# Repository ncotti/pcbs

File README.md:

# PCBS

PCB boards designed with KiCad.

https://www.youtube.com/watch?v=Poj4V9u9bMg

## Version numbering

V0.X

Refers to prototypes that have not being produced, soldered and tested. Being v0.0 the first prototype.

V1.0 is the version of the schematic that has been produced and tested.

V1.x are iterations of a working design.

v2.x are versions that changed something substancial.

## Best way to share libraries between projects

So, you have your library in a defined path, and you go to File->Add library.

When doing this, you will see that the library has been added with an absolute path (Preferences -> Manage Footprint libraries).

The steps to take are as follows:

Open the project. Go to "Preferences -> Configure Paths..." and define these three new variables:

| Name                      | Path                          |
|:--------------------------|:------------------------------|
| KICAD_USER_SYMBOL_DIR     | <path_to_library>/symbols     |
| KICAD_USER_FOOTPRINT_DIR  | <path_to_library>/footprints  |
| KICAD_USER_3DMODEL_DIR    | <path_to_library>/3d_models   |

After that, the libraries should be loaded.

### Creating new libraries steps

You can create a new library like "File -> New Library... -> Global". Then, choose the name you like, and save it in `<path_to_library>/symbols/<lib_name>`.

If you previously defined the environmental variables, KICAD will autocomplete the path with ${KICAD_USER_SYMBOL_DIR}/<lib_name>. Go check it out at "Preferences -> Manage Symbol Libraries".

Then, go to the "Footprint Editor". The same procedure as with the symbol libraries apply.

Finally, when importing 3D files, the enviromental variable should also autocomplete with `${KICAD_USER_3DMODEL_DIR}/<3d_file>`.

### Footprint parts: M L normal

When importing footprints, some appear with "M" "L" or normal.

This letters stand for:

* M: Most land protrusion (bigger pads)
* N (or no letter): Nominal land protrusion (normal pads)
* L: Least land protrusion (smaller pads)

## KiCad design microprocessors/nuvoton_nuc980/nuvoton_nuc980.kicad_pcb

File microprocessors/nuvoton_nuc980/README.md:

# NUC980

Documentation:

https://www.nuvoton.com/products/microprocessors/arm9-mpus/nuc980-industrial-control-iot-series/nuc980dk63yc/?group=Document&tab=2

NuMaker-IIoT-NUC980

https://www.techdesign.com/market/nuvoton/product-detail/ntc000092/numaker-iiot-nuc980?packing=No%20Packing

https://www.nuvoton.com/products/iot-solution/iot-platform/numaker-iiot-nuc980/

## Parallel LDOs

https://techweb.rohm.com/product/power-ic/dcdc/9235/

You can't connect the two LDO outputs together, because you can't guaranty that both will have exactly the same voltage value.

Following the diagram above, we can expect the middle point, after the ballast resistors, to be at the same "Vout" potential:

$$ V_{out} = V_1 - I_1 \cdot R = V_2 - I_2 \cdot R$$

$$ R = \frac{V_2 - V_1}{I_2 - I_1}$$

We go to the datasheet and find the "CD output accuracy"

We want two metrics here: 

1. Voltage range at the output.
2. Maximum current at the output.

The worst case would be:

$$V_2 = V_{0} + \Delta V $$
$$V_1 = V_{0} - \Delta V $$

$$ R = \frac{2 \cdot \Delta V}{I_2 - I_1} $$

It would be great to say: "hey make the current difference equal to 0". However, that would imply a value of "R" infinitely big.

The bigger "R", the more equal the currents are. However, the bigger the R, the bigger the voltage drop at the output.

Given a desired output current $I_{out}$, which must be greater than the maximum current of the LDO $I_{LDO}$, the difference in current must be less than the current required by the two LDOs.

For example, if LDO max current is 300 mA, and I want 500mA, then the difference must be less than 100mA, because one will be providing 300mA and the other 200mA.

$$(\Delta I = \frac{2\Delta V}{R} ) \le 2\cdot I_{max} - I_{out} $$

$$ R \ge \frac{2\Delta V}{2\cdot I_{max} - I_{out}} $$

Then:

$$ I_{out} = I_1 + I_2 = \frac{V_1 - V_{out}}{R} + \frac{V_2 - V_{out}}{R} $$

$$ I_{out} = \frac{V_0 - \Delta V - V_{out}}{R} + \frac{V_0 + \Delta V - V_{out}}{R}$$

$$ I_{out} = 2 \frac{V_0 - V_{out}}{R} $$

$$ V_0 - V_{out} = I_{out} \cdot R / 2 $$

Other design parameter is how much you desire the output voltage to swing. If the accuracy of the LDO is 1%, well maybe you can afford to lose 3% or 5%, depending on the minimum voltage required by your devices:

$$ (\Delta V_{out-actual} = I_{out} \cdot R / 2) \le \Delta V_{out} $$

Despejando "R":

$$ R \le \frac{2 \Delta V_{out}}{I_{out}}$$

Therefore:

$$\frac{2\Delta V}{2\cdot I_{max} - I_{out}} \le R \le \frac{2 \Delta V_{out}}{I_{out}} $$

And that's the design equation:

Your inputs are:

* $\Delta V_{out}$: Maximum tolerated voltage drop from the nominal voltage of the LDO at the output.
* $I_{out}$: Maximum current consumed by the load.

And then $\Delta V$ and $I_{max}$ are the precision and maximum current of the LDO as stated in the datasheet.

You always want the minimum value of "R" possible, that still satisfies the inequation.

If using:

$$ 2 * 3.3 * 0.014 / (2 * 300m - 450m) < R < 2 * 200m / 450m$$

$$ 0.616 <= R <= 0.89 $$

https://www.youtube.com/watch?v=H4nrotIVuUM

https://abracon.com/uploads/resources/Ferrite-Beads-White-Paper.pdf

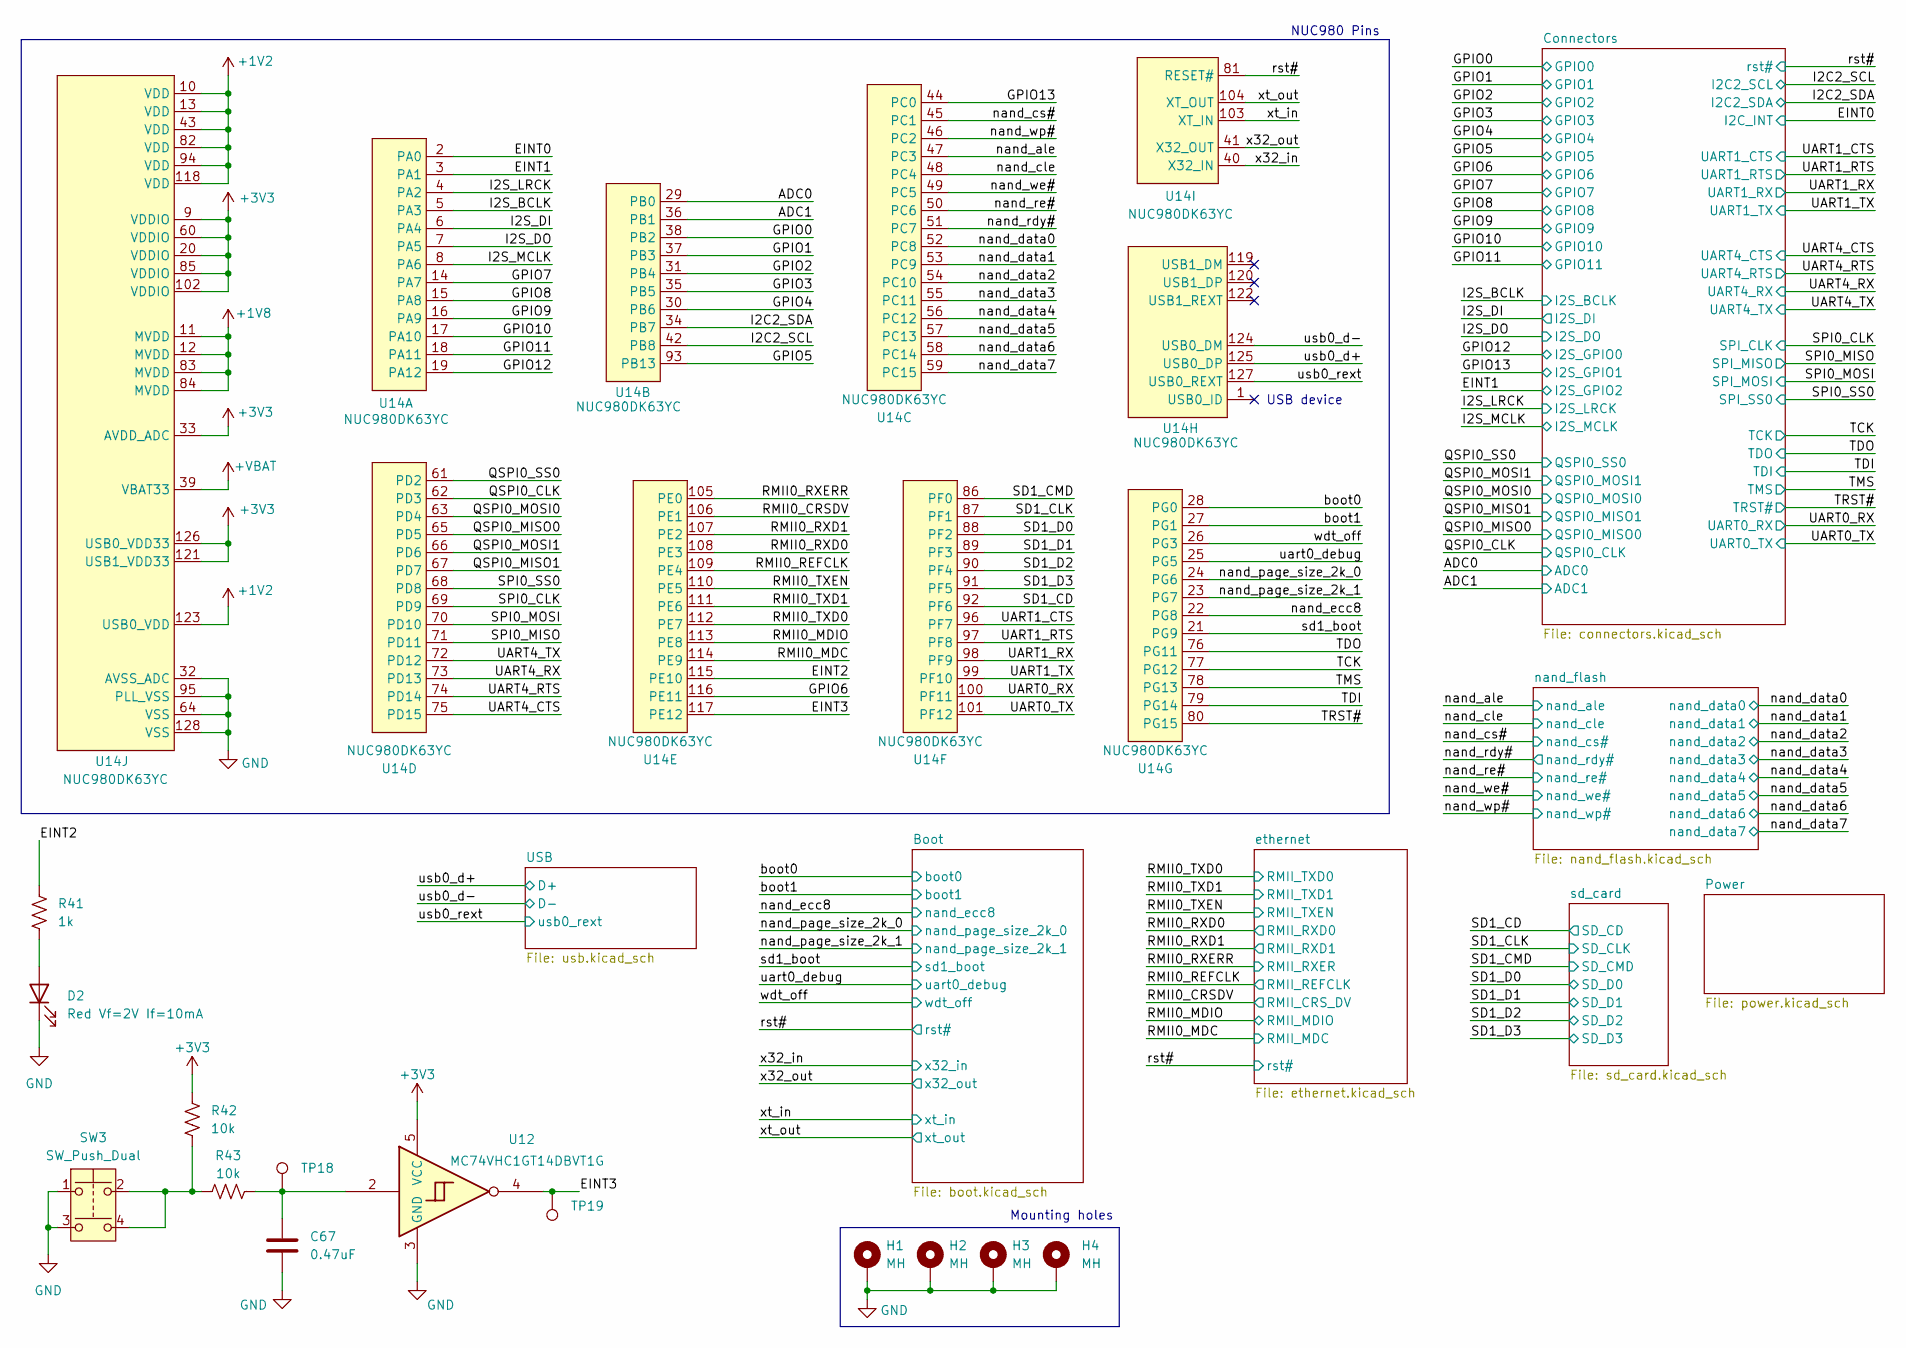
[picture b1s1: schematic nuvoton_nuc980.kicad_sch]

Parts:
C67: 0.47uF; C_0805_2012Metric_Pad1.18x1.45mm_HandSolder; Mfr. P/N CL21B474KAFNNNG
D2: Red Vf=2V If=10mA; LED_0603_1608Metric_Pad1.05x0.95mm_HandSolder; Mfr. P/N B1911USD-20D000114U1930
H1, H2, H3, H4: MH
R41: 1k; R_0805_2012Metric_Pad1.20x1.40mm_HandSolder; Mfr. P/N RC0805FR-101KL
R42, R43: 10k; R_0805_2012Metric_Pad1.20x1.40mm_HandSolder; Mfr. P/N RC0805FR-1310KL
SW3: SW_Push_Dual; SW_PUSH_6mm_H5mm; Mfr. P/N TS02-66-60-BK-260-SCR-D
TP18, TP19: TestPoint; TestPoint_Pad_D2.0mm
U12: MC74VHC1GT14DBVT1G; SC-74A-5_1.55x2.9mm_P0.95mm; Mfr. P/N MC74VHC1GT14DBVT1G
U14: NUC980DK63YC; LQFP-128_14x14mm_P0.4mm; Mfr. P/N NUC980DK63YC; Digikey P/N 816-NUC980DK63YC-ND

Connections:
+1V2: U14.10 (VDD), U14.13 (VDD), U14.43 (VDD), U14.82 (VDD), U14.94 (VDD), U14.118 (VDD), U14.123 (USB0_VDD); also elsewhere on the board
+1V8: U14.11 (MVDD), U14.12 (MVDD), U14.83 (MVDD), U14.84 (MVDD); also elsewhere on the board
+3V3: R42.1, U12.5 (VCC), U14.9 (VDDIO), U14.20 (VDDIO), U14.33 (AVDD_ADC), U14.60 (VDDIO), U14.85 (VDDIO), U14.102 (VDDIO), U14.121 (USB1_VDD33), U14.126 (USB0_VDD33); also elsewhere on the board
+VBAT: U14.39 (VBAT33); also elsewhere on the board
/ADC0: U14.29 (PB0); also elsewhere on the board
/ADC1: U14.36 (PB1); also elsewhere on the board
/EINT0: U14.2 (PA0); also elsewhere on the board
/EINT1: U14.3 (PA1); also elsewhere on the board
/EINT2: R41.1, U14.115 (PE10)
/EINT3: TP19.1, U12.4, U14.117 (PE12)
/GPIO0: U14.38 (PB2); also elsewhere on the board
/GPIO1: U14.37 (PB3); also elsewhere on the board
/GPIO2: U14.31 (PB4); also elsewhere on the board
/GPIO3: U14.35 (PB5); also elsewhere on the board
/GPIO4: U14.30 (PB6); also elsewhere on the board
/GPIO5: U14.93 (PB13); also elsewhere on the board
/GPIO6: U14.116 (PE11); also elsewhere on the board
/GPIO7: U14.14 (PA7); also elsewhere on the board
/GPIO8: U14.15 (PA8); also elsewhere on the board
/GPIO9: U14.16 (PA9); also elsewhere on the board
/GPIO10: U14.17 (PA10); also elsewhere on the board
/GPIO11: U14.18 (PA11); also elsewhere on the board
/GPIO12: U14.19 (PA12); also elsewhere on the board
/GPIO13: U14.44 (PC0); also elsewhere on the board
/I2C2_SCL: U14.42 (PB8); also elsewhere on the board
/I2C2_SDA: U14.34 (PB7); also elsewhere on the board
/I2S_BCLK: U14.5 (PA3); also elsewhere on the board
/I2S_DI: U14.6 (PA4); also elsewhere on the board
/I2S_DO: U14.7 (PA5); also elsewhere on the board
/I2S_LRCK: U14.4 (PA2); also elsewhere on the board
/I2S_MCLK: U14.8 (PA6); also elsewhere on the board
/QSPI0_CLK: U14.62 (PD3); also elsewhere on the board
/QSPI0_MISO0: U14.65 (PD5); also elsewhere on the board
/QSPI0_MISO1: U14.67 (PD7); also elsewhere on the board
/QSPI0_MOSI0: U14.63 (PD4); also elsewhere on the board
/QSPI0_MOSI1: U14.66 (PD6); also elsewhere on the board
/QSPI0_SS0: U14.61 (PD2); also elsewhere on the board
/RMII0_CRSDV: U14.106 (PE1); also elsewhere on the board
/RMII0_MDC: U14.114 (PE9); also elsewhere on the board
/RMII0_MDIO: U14.113 (PE8); also elsewhere on the board
/RMII0_REFCLK: U14.109 (PE4); also elsewhere on the board
/RMII0_RXD0: U14.108 (PE3); also elsewhere on the board
/RMII0_RXD1: U14.107 (PE2); also elsewhere on the board
/RMII0_RXERR: U14.105 (PE0); also elsewhere on the board
/RMII0_TXD0: U14.112 (PE7); also elsewhere on the board
/RMII0_TXD1: U14.111 (PE6); also elsewhere on the board
/RMII0_TXEN: U14.110 (PE5); also elsewhere on the board
/SD1_CD: U14.92 (PF6); also elsewhere on the board
/SD1_CLK: U14.87 (PF1); also elsewhere on the board
/SD1_CMD: U14.86 (PF0); also elsewhere on the board
/SD1_D0: U14.88 (PF2); also elsewhere on the board
/SD1_D1: U14.89 (PF3); also elsewhere on the board
/SD1_D2: U14.90 (PF4); also elsewhere on the board
/SD1_D3: U14.91 (PF5); also elsewhere on the board
/SPI0_CLK: U14.69 (PD9); also elsewhere on the board
/SPI0_MISO: U14.71 (PD11); also elsewhere on the board
/SPI0_MOSI: U14.70 (PD10); also elsewhere on the board
/SPI0_SS0: U14.68 (PD8); also elsewhere on the board
/TCK: U14.77 (PG12); also elsewhere on the board
/TDI: U14.79 (PG14); also elsewhere on the board
/TDO: U14.76 (PG11); also elsewhere on the board
/TMS: U14.78 (PG13); also elsewhere on the board
/TRST#: U14.80 (PG15); also elsewhere on the board
/UART0_RX: U14.100 (PF11); also elsewhere on the board
/UART0_TX: U14.101 (PF12); also elsewhere on the board
/UART1_CTS: U14.96 (PF7); also elsewhere on the board
/UART1_RTS: U14.97 (PF8); also elsewhere on the board
/UART1_RX: U14.98 (PF9); also elsewhere on the board
/UART1_TX: U14.99 (PF10); also elsewhere on the board
/UART4_CTS: U14.75 (PD15); also elsewhere on the board
/UART4_RTS: U14.74 (PD14); also elsewhere on the board
/UART4_RX: U14.73 (PD13); also elsewhere on the board
/UART4_TX: U14.72 (PD12); also elsewhere on the board
/boot0: U14.28 (PG0); also elsewhere on the board
/boot1: U14.27 (PG1); also elsewhere on the board
/nand_ale: U14.47 (PC3); also elsewhere on the board
/nand_cle: U14.48 (PC4); also elsewhere on the board
/nand_cs#: U14.45 (PC1); also elsewhere on the board
/nand_data0: U14.52 (PC8); also elsewhere on the board
/nand_data1: U14.53 (PC9); also elsewhere on the board
/nand_data2: U14.54 (PC10); also elsewhere on the board
/nand_data3: U14.55 (PC11); also elsewhere on the board
/nand_data4: U14.56 (PC12); also elsewhere on the board
/nand_data5: U14.57 (PC13); also elsewhere on the board
/nand_data6: U14.58 (PC14); also elsewhere on the board
/nand_data7: U14.59 (PC15); also elsewhere on the board
/nand_ecc8: U14.22 (PG8); also elsewhere on the board
/nand_page_size_2k_0: U14.24 (PG6); also elsewhere on the board
/nand_page_size_2k_1: U14.23 (PG7); also elsewhere on the board
/nand_rdy#: U14.51 (PC7); also elsewhere on the board
/nand_re#: U14.50 (PC6); also elsewhere on the board
/nand_we#: U14.49 (PC5); also elsewhere on the board
/nand_wp#: U14.46 (PC2); also elsewhere on the board
/rst#: U14.81 (RESET#); also elsewhere on the board
/sd1_boot: U14.21 (PG9); also elsewhere on the board
/uart0_debug: U14.25 (PG5); also elsewhere on the board
/usb0_d+: U14.125 (USB0_DP); also elsewhere on the board
/usb0_d-: U14.124 (USB0_DM); also elsewhere on the board
/usb0_rext: U14.127 (USB0_REXT); also elsewhere on the board
/wdt_off: U14.26 (PG3); also elsewhere on the board
/x32_in: U14.40 (X32_IN); also elsewhere on the board
/x32_out: U14.41 (X32_OUT); also elsewhere on the board
/xt_in: U14.103 (XT_IN); also elsewhere on the board
/xt_out: U14.104 (XT_OUT); also elsewhere on the board
GND: C67.2, D2.1 (K), H1.1, H2.1, H3.1, H4.1, SW3.1, SW3.3, U12.3 (GND), U14.32 (AVSS_ADC), U14.64 (VSS), U14.95 (PLL_VSS), U14.128 (VSS); also elsewhere on the board
unnamed: C67.1, R43.2, TP18.1, U12.2
unnamed: D2.2 (A), R41.2
unnamed: R42.2, R43.1, SW3.2, SW3.4

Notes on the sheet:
NUC980 Pins
Mounting holes
USB device

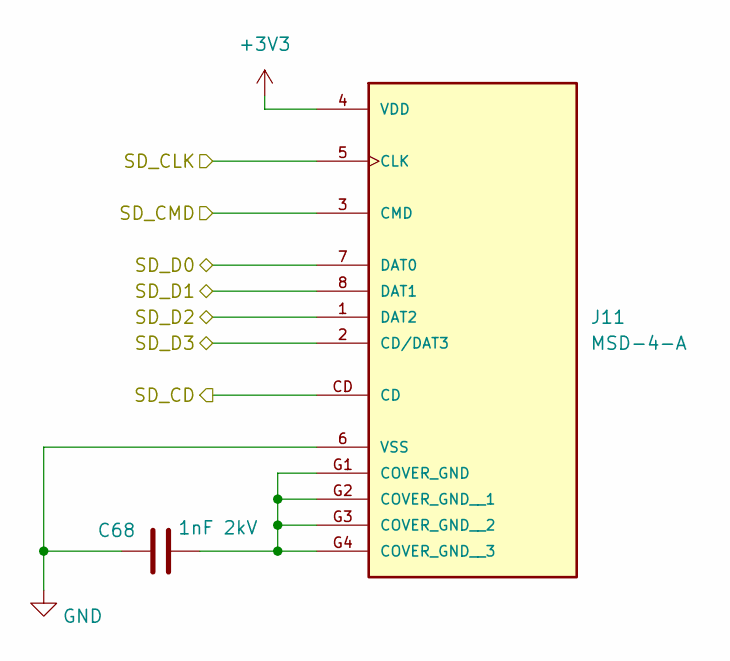
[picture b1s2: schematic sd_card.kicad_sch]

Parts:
C68: 1nF 2kV; C_1206_3216Metric_Pad1.33x1.80mm_HandSolder; Mfr. P/N 1206B102M202CT
J11: MSD-4-A; CUI_MSD-4-A; Mfr. P/N MSD-4-A

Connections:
+3V3: J11.4 (VDD); also elsewhere on the board
/SD1_CD: J11.CD; also elsewhere on the board
/SD1_CLK: J11.5 (CLK); also elsewhere on the board
/SD1_CMD: J11.3 (CMD); also elsewhere on the board
/SD1_D0: J11.7 (DAT0); also elsewhere on the board
/SD1_D1: J11.8 (DAT1); also elsewhere on the board
/SD1_D2: J11.1 (DAT2); also elsewhere on the board
/SD1_D3: J11.2 (CD/DAT3); also elsewhere on the board
GND: C68.1, J11.6 (VSS); also elsewhere on the board
unnamed: C68.2, J11.G1 (COVER_GND), J11.G2 (COVER_GND__1), J11.G3 (COVER_GND__2), J11.G4 (COVER_GND__3)

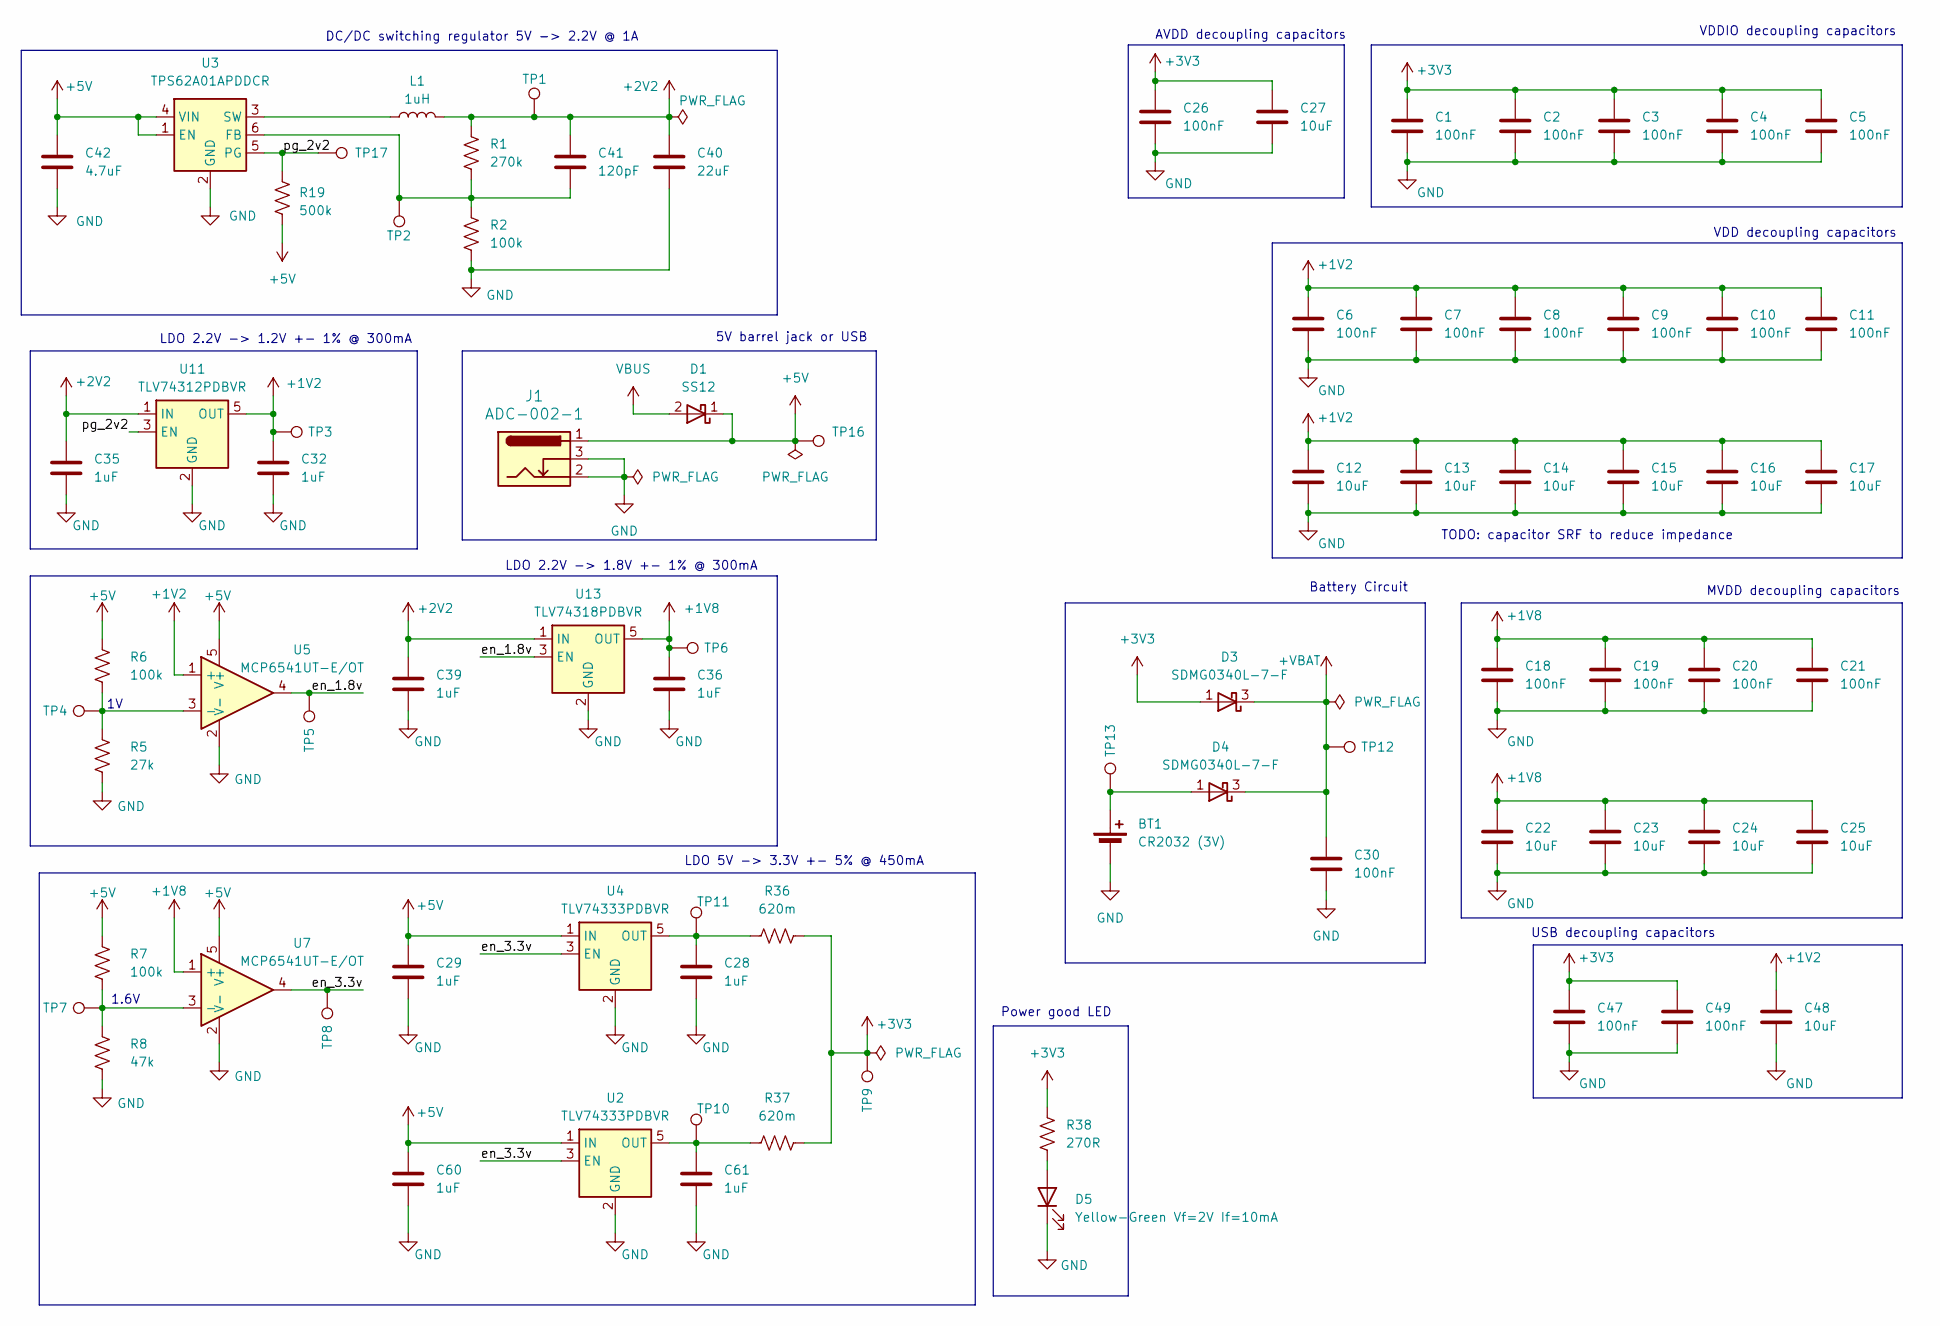
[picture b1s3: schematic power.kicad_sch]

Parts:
BT1: CR2032 (3V); BAT_BH-25C-1; Mfr. P/N BH-25C-1
C1, C2, C3, C4, C5, C6, C7, C8, C9, C10, C11, C18, C19, C20, C21, C26, C30, C47, C49: 100nF; C_0805_2012Metric_Pad1.18x1.45mm_HandSolder; Mfr. P/N CL21B104KACNNNC
C12, C13, C14, C15, C16, C17, C22, C23, C24, C25, C27, C48: 10uF; C_0805_2012Metric_Pad1.18x1.45mm_HandSolder; Mfr. P/N CL21B106KOQNNNE
C28, C29, C32, C35, C36, C39, C60, C61: 1uF; C_0805_2012Metric_Pad1.18x1.45mm_HandSolder; Mfr. P/N CL21B105KBFNNNE
C40: 22uF; C_0805_2012Metric_Pad1.18x1.45mm_HandSolder; Mfr. P/N CL21A226MAYNNNE
C41: 120pF; C_0805_2012Metric_Pad1.18x1.45mm_HandSolder; Mfr. P/N C0805C121K5HACTU
C42: 4.7uF; C_0805_2012Metric_Pad1.18x1.45mm_HandSolder; Mfr. P/N CL21A475KPFNNNE
D1: SS12; D_SMA_Handsoldering; Mfr. P/N SS12
D3, D4: SDMG0340L-7-F; SOT-323_SC-70_Handsoldering; Mfr. P/N SDMG0340L-7-F
D5: Yellow-Green Vf=2V If=10mA; LED_0603_1608Metric_Pad1.05x0.95mm_HandSolder; Mfr. P/N B1911UYG-20D000114U1930
J1: ADC-002-1; Mfr. P/N ADC-002-1
L1: 1uH; L_0805_2012Metric_Pad1.05x1.20mm_HandSolder; Mfr. P/N MLZ2012A1R0WT000
R1: 270k; R_0805_2012Metric_Pad1.20x1.40mm_HandSolder; Mfr. P/N RC0805FR-13270KL
R2, R6, R7: 100k; R_0805_2012Metric_Pad1.20x1.40mm_HandSolder; Mfr. P/N AC0805FR-13100KL
R5: 27k; R_0805_2012Metric_Pad1.20x1.40mm_HandSolder; Mfr. P/N RC0805FR-1327KL
R8: 47k; R_0805_2012Metric_Pad1.20x1.40mm_HandSolder; Mfr. P/N RC0805FR-1347KL
R19: 500k; R_0805_2012Metric_Pad1.20x1.40mm_HandSolder; Mfr. P/N RC0805FR-07499KL
R36, R37: 620m; R_0805_2012Metric_Pad1.20x1.40mm_HandSolder; Mfr. P/N CRL0805-FW-R620ELF
R38: 270R; R_0805_2012Metric_Pad1.20x1.40mm_HandSolder; Mfr. P/N RC0805FR-10270RL
TP1, TP2, TP3, TP4, TP5, TP6, TP7, TP8, TP9, TP10, TP11, TP12, TP13, TP16, TP17: TestPoint; TestPoint_Pad_D2.0mm
U2, U4: TLV74333PDBVR; SOT-23-5; Mfr. P/N TLV74333PDBVR
U3: TPS62A01APDDCR; TSOT-23-6_HandSoldering; Mfr. P/N TPS62A01APDDCR
U5, U7: MCP6541UT-E/OT; SOT-23-5_HandSoldering; Mfr. P/N MCP6541UT-E/OT
U11: TLV74312PDBVR; SOT-23-5; Mfr. P/N TLV74312PDBVR
U13: TLV74318PDBVR; SOT-23-5; Mfr. P/N TLV74318PDBVR

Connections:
+1V2: C6.1, C7.1, C8.1, C9.1, C10.1, C11.1, C12.1, C13.1, C14.1, C15.1, C16.1, C17.1, C32.1, C48.1, TP3.1, U5.1 (+), U11.5 (OUT); also elsewhere on the board
+1V8: C18.1, C19.1, C20.1, C21.1, C22.1, C23.1, C24.1, C25.1, C36.1, TP6.1, U7.1 (+), U13.5 (OUT); also elsewhere on the board
+2V2: C35.1, C39.1, C40.1, C41.1, L1.2, R1.1, TP1.1, U11.1 (IN), U13.1 (IN)
+3V3: C1.1, C2.1, C3.1, C4.1, C5.1, C26.1, C27.1, C47.1, C49.1, D3.1, R36.2, R37.2, R38.1, TP9.1; also elsewhere on the board
+5V: C29.1, C42.1, C60.1, D1.1, J1.1, R6.1, R7.1, R19.2, TP16.1, U2.1 (IN), U3.1 (EN), U3.4 (VIN), U4.1 (IN), U5.5 (V+), U7.5 (V+)
+VBAT: C30.1, D3.3, D4.3, TP12.1; also elsewhere on the board
/Power/en_1.8v: TP5.1, U5.4, U13.3 (EN)
/Power/en_3.3v: TP8.1, U2.3 (EN), U4.3 (EN), U7.4
/Power/pg_2v2: R19.1, TP17.1, U3.5 (PG), U11.3 (EN)
GND: BT1.N (-), C1.2, C2.2, C3.2, C4.2, C5.2, C6.2, C7.2, C8.2, C9.2, C10.2, C11.2, C12.2, C13.2, C14.2, C15.2, C16.2, C17.2, C18.2, C19.2, C20.2, C21.2, C22.2, C23.2, C24.2, C25.2, C26.2, C27.2, C28.2, C29.2, C30.2, C32.2, C35.2, C36.2, C39.2, C40.2, C42.2, C47.2, C48.2, C49.2, C60.2, C61.2, D5.1 (K), J1.2, J1.3, R2.2, R5.2, R8.2, U2.2 (GND), U3.2 (GND), U4.2 (GND), U5.2 (V-), U7.2 (V-), U11.2 (GND), U13.2 (GND); also elsewhere on the board
unnamed: BT1.P (+), D4.1, TP13.1
unnamed: D5.2 (A), R38.2
unnamed: C61.1, R37.1, TP10.1, U2.5 (OUT)
unnamed: C41.2, R1.2, R2.1, TP2.1, U3.6 (FB)
unnamed: L1.1, U3.3 (SW)
unnamed: C28.1, R36.1, TP11.1, U4.5 (OUT)
unnamed: R5.1, R6.2, TP4.1, U5.3 (-)
unnamed: R7.2, R8.1, TP7.1, U7.3 (-)
VBUS: D1.2; also elsewhere on the board

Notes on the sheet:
LDO 2.2V -> 1.8V +- 1% @ 300mA
5V barrel jack or USB
TODO: capacitor SRF to reduce impedance
VDD decoupling capacitors
Power good LED
USB decoupling capacitors
LDO 2.2V -> 1.2V +- 1% @ 300mA
Battery Circuit
1.6V
DC/DC switching regulator 5V -> 2.2V @ 1A
MVDD decoupling capacitors
AVDD decoupling capacitors
VDDIO decoupling capacitors
LDO 5V -> 3.3V +- 5% @ 450mA

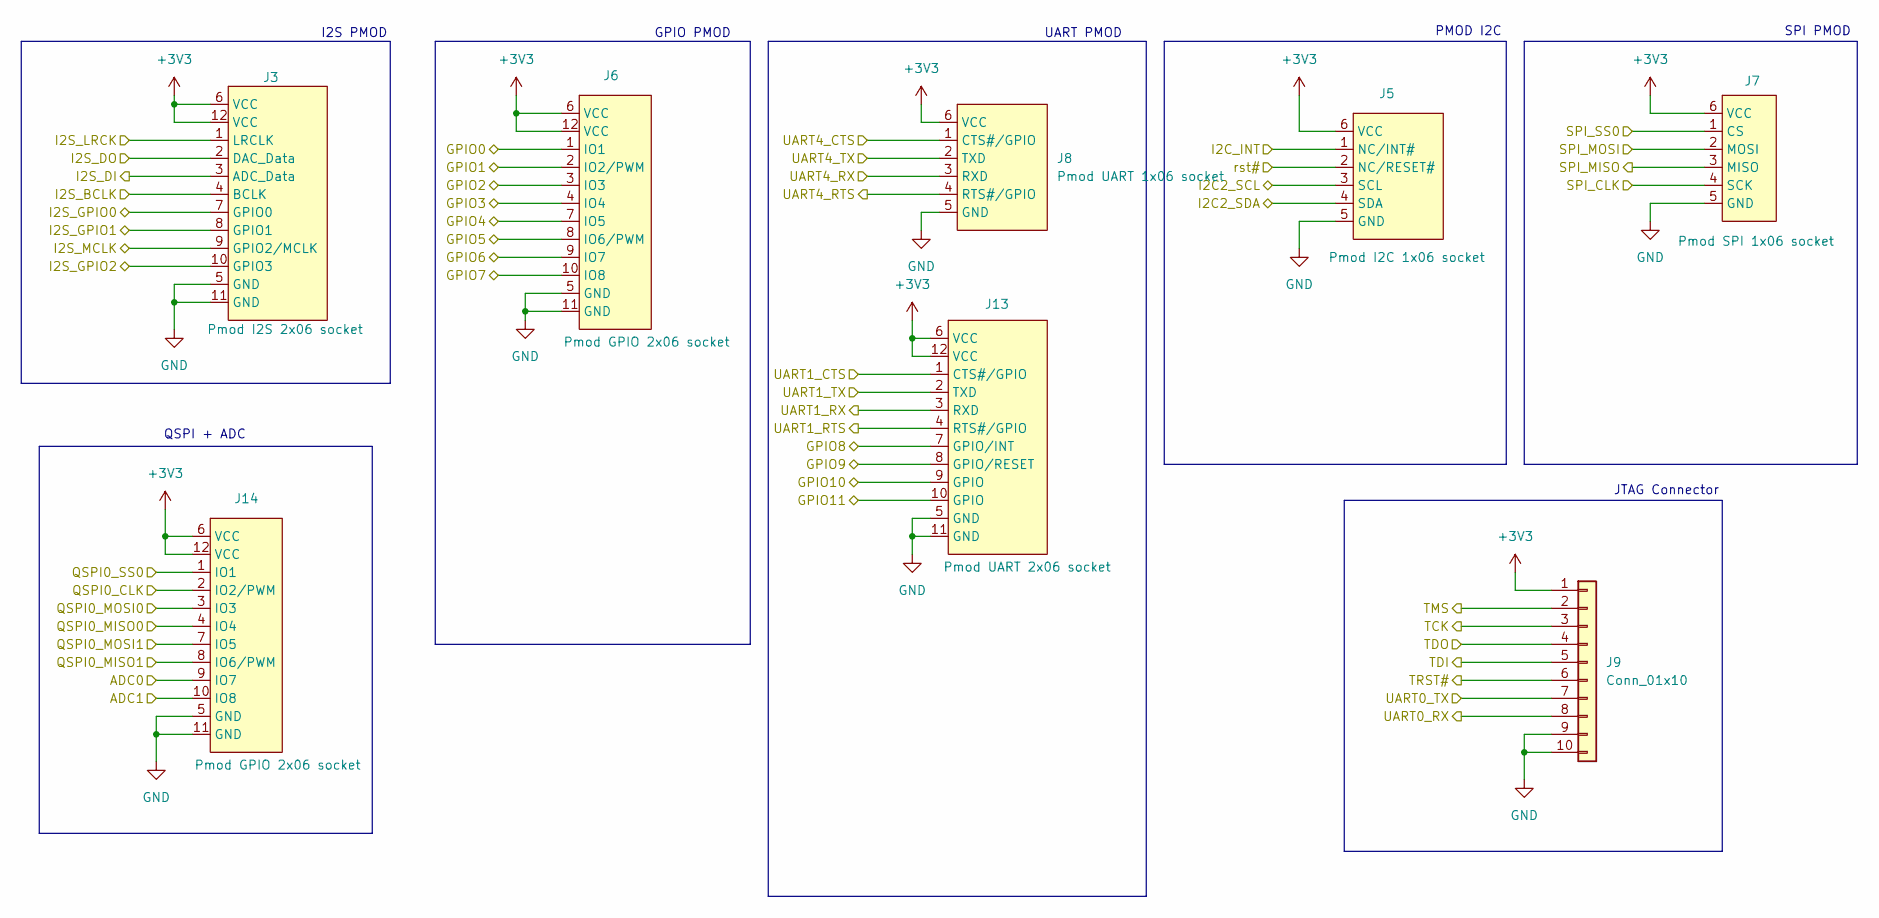
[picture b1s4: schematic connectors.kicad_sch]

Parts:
J3: Pmod I2S 2x06 socket; Pmod_2x06_socket; Mfr. P/N PH2RA-12-UA
J5: Pmod I2C 1x06 socket; Pmod_1x06_socket; Mfr. P/N 613006143121
J6, J14: Pmod GPIO 2x06 socket; Pmod_2x06_socket; Mfr. P/N 613012243121
J7: Pmod SPI 1x06 socket; Pmod_1x06_socket; Mfr. P/N 613006143121
J8: Pmod UART 1x06 socket; Pmod_1x06_socket; Mfr. P/N 613006143121
J9: Conn_01x10; PinHeader_1x10_P2.54mm_Vertical
J13: Pmod UART 2x06 socket; Pmod_2x06_socket; Mfr. P/N 613012243121

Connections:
+3V3: J3.6 (VCC), J3.12 (VCC), J5.6 (VCC), J6.6 (VCC), J6.12 (VCC), J7.6 (VCC), J8.6 (VCC), J9.1, J13.6 (VCC), J13.12 (VCC), J14.6 (VCC), J14.12 (VCC); also elsewhere on the board
/ADC0: J14.9 (IO7); also elsewhere on the board
/ADC1: J14.10 (IO8); also elsewhere on the board
/EINT0: J5.1 (NC/INT#); also elsewhere on the board
/EINT1: J3.10 (GPIO3); also elsewhere on the board
/GPIO0: J6.1 (IO1); also elsewhere on the board
/GPIO1: J6.2 (IO2/PWM); also elsewhere on the board
/GPIO2: J6.3 (IO3); also elsewhere on the board
/GPIO3: J6.4 (IO4); also elsewhere on the board
/GPIO4: J6.7 (IO5); also elsewhere on the board
/GPIO5: J6.8 (IO6/PWM); also elsewhere on the board
/GPIO6: J6.9 (IO7); also elsewhere on the board
/GPIO7: J6.10 (IO8); also elsewhere on the board
/GPIO8: J13.7 (GPIO/INT); also elsewhere on the board
/GPIO9: J13.8 (GPIO/RESET); also elsewhere on the board
/GPIO10: J13.9 (GPIO); also elsewhere on the board
/GPIO11: J13.10 (GPIO); also elsewhere on the board
/GPIO12: J3.7 (GPIO0); also elsewhere on the board
/GPIO13: J3.8 (GPIO1); also elsewhere on the board
/I2C2_SCL: J5.3 (SCL); also elsewhere on the board
/I2C2_SDA: J5.4 (SDA); also elsewhere on the board
/I2S_BCLK: J3.4 (BCLK); also elsewhere on the board
/I2S_DI: J3.3 (ADC_Data); also elsewhere on the board
/I2S_DO: J3.2 (DAC_Data); also elsewhere on the board
/I2S_LRCK: J3.1 (LRCLK); also elsewhere on the board
/I2S_MCLK: J3.9 (GPIO2/MCLK); also elsewhere on the board
/QSPI0_CLK: J14.2 (IO2/PWM); also elsewhere on the board
/QSPI0_MISO0: J14.4 (IO4); also elsewhere on the board
/QSPI0_MISO1: J14.8 (IO6/PWM); also elsewhere on the board
/QSPI0_MOSI0: J14.3 (IO3); also elsewhere on the board
/QSPI0_MOSI1: J14.7 (IO5); also elsewhere on the board
/QSPI0_SS0: J14.1 (IO1); also elsewhere on the board
/SPI0_CLK: J7.4 (SCK); also elsewhere on the board
/SPI0_MISO: J7.3 (MISO); also elsewhere on the board
/SPI0_MOSI: J7.2 (MOSI); also elsewhere on the board
/SPI0_SS0: J7.1 (CS); also elsewhere on the board
/TCK: J9.3; also elsewhere on the board
/TDI: J9.5; also elsewhere on the board
/TDO: J9.4; also elsewhere on the board
/TMS: J9.2; also elsewhere on the board
/TRST#: J9.6; also elsewhere on the board
/UART0_RX: J9.8; also elsewhere on the board
/UART0_TX: J9.7; also elsewhere on the board
/UART1_CTS: J13.1 (CTS#/GPIO); also elsewhere on the board
/UART1_RTS: J13.4 (RTS#/GPIO); also elsewhere on the board
/UART1_RX: J13.3 (RXD); also elsewhere on the board
/UART1_TX: J13.2 (TXD); also elsewhere on the board
/UART4_CTS: J8.1 (CTS#/GPIO); also elsewhere on the board
/UART4_RTS: J8.4 (RTS#/GPIO); also elsewhere on the board
/UART4_RX: J8.3 (RXD); also elsewhere on the board
/UART4_TX: J8.2 (TXD); also elsewhere on the board
/rst#: J5.2 (NC/RESET#); also elsewhere on the board
GND: J3.5 (GND), J3.11 (GND), J5.5 (GND), J6.5 (GND), J6.11 (GND), J7.5 (GND), J8.5 (GND), J9.9, J9.10, J13.5 (GND), J13.11 (GND), J14.5 (GND), J14.11 (GND); also elsewhere on the board

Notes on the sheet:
SPI PMOD
I2S PMOD
JTAG Connector
PMOD I2C
GPIO PMOD
QSPI + ADC
UART PMOD

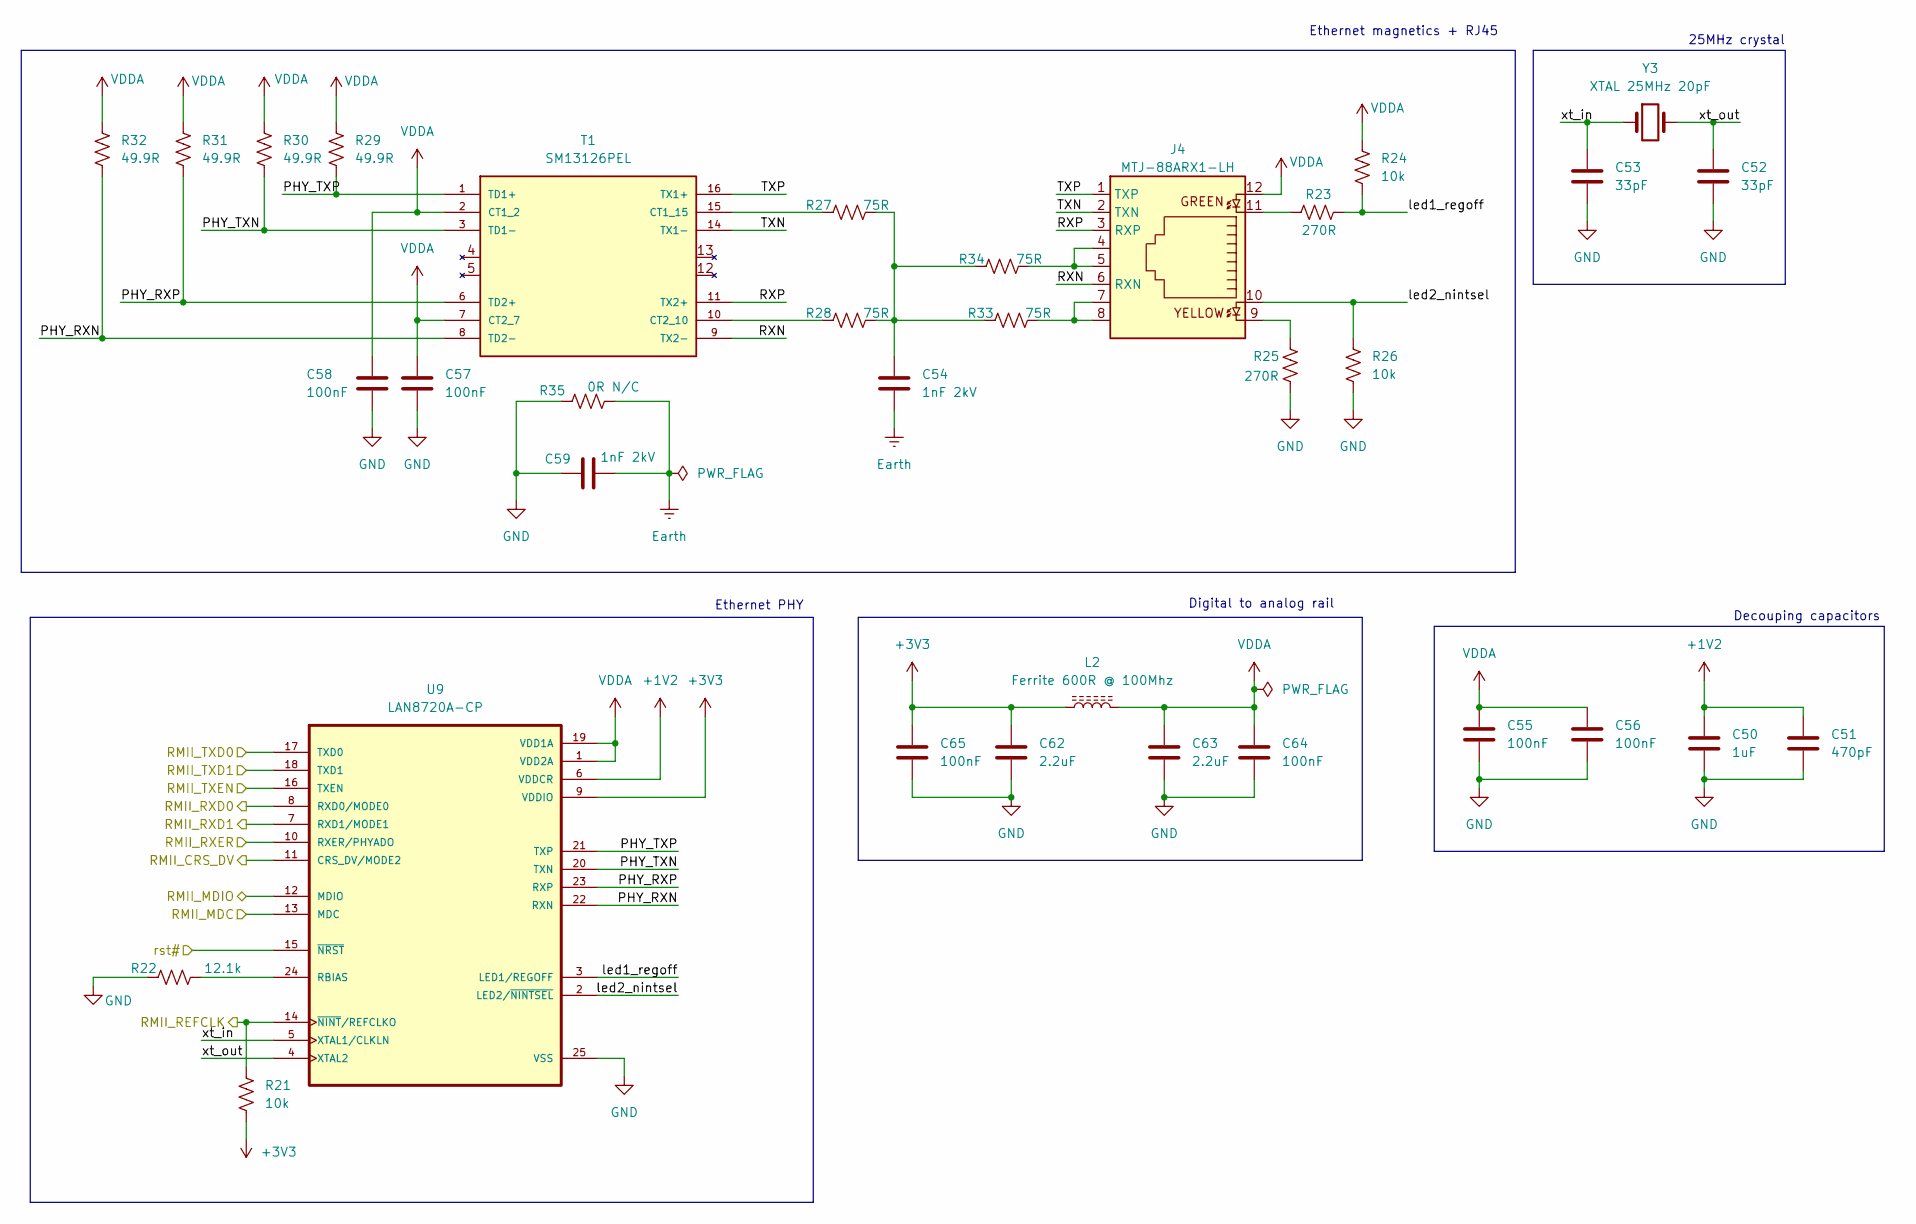
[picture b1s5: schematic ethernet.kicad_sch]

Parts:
C50: 1uF; C_0805_2012Metric_Pad1.18x1.45mm_HandSolder; Mfr. P/N CL21B105KBFNNNE
C51: 470pF; C_0805_2012Metric_Pad1.18x1.45mm_HandSolder; Mfr. P/N 0805B471K500CT
C52, C53: 33pF; C_0805_2012Metric_Pad1.18x1.45mm_HandSolder; Mfr. P/N CC0805JRNPO9BN330
C54, C59: 1nF 2kV; C_1206_3216Metric_Pad1.33x1.80mm_HandSolder; Mfr. P/N 1206B102M202CT
C55, C56, C57, C58, C64, C65: 100nF; C_0805_2012Metric_Pad1.18x1.45mm_HandSolder; Mfr. P/N CL21B104KACNNNC
C62, C63: 2.2uF; C_0805_2012Metric_Pad1.18x1.45mm_HandSolder; Mfr. P/N GMC21X7R225K25NT
J4: MTJ-88ARX1-LH; RJ45_MTJ-88ARX1-LH_ADM; Mfr. P/N MTJ-88ARX1-LH
L2: Ferrite 600R @ 100Mhz; L_0805_2012Metric_Pad1.05x1.20mm_HandSolder; Mfr. P/N WLBD2012HCU601TH
R21, R24, R26: 10k; R_0805_2012Metric_Pad1.20x1.40mm_HandSolder; Mfr. P/N RC0805FR-1310KL
R22: 12.1k; R_0805_2012Metric_Pad1.20x1.40mm_HandSolder; Mfr. P/N AC0805FR-0712K1L
R23, R25: 270R; R_0805_2012Metric_Pad1.20x1.40mm_HandSolder; Mfr. P/N RC0805FR-10270RL
R27, R28, R33, R34: 75R; R_0805_2012Metric_Pad1.20x1.40mm_HandSolder; Mfr. P/N RC0805FR-1375RL
R29, R30, R31, R32: 49.9R; R_0805_2012Metric_Pad1.20x1.40mm_HandSolder; Mfr. P/N RC0805FR-1349R9L
R35: 0R N/C; R_0805_2012Metric_Pad1.20x1.40mm_HandSolder; Mfr. P/N RMCF0805ZG0R00
T1: SM13126PEL; XFMR_SM13126PEL; Mfr. P/N SM13126PEL
U9: LAN8720A-CP; QFN50P400X400X100-25N; Mfr. P/N LAN8720A-CP
Y3: XTAL 25MHz 20pF; Crystal_SMD_HC49-SD_HandSoldering; Mfr. P/N 25M20P2/49SMT

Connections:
+1V2: C50.1, C51.1, U9.6 (VDDCR); also elsewhere on the board
+3V3: C62.1, C65.1, L2.1, R21.2, U9.9 (VDDIO); also elsewhere on the board
/RMII0_CRSDV: U9.11 (CRS_DV/MODE2); also elsewhere on the board
/RMII0_MDC: U9.13 (MDC); also elsewhere on the board
/RMII0_MDIO: U9.12 (MDIO); also elsewhere on the board
/RMII0_REFCLK: R21.1, U9.14 (~NINT/REFCLKO); also elsewhere on the board
/RMII0_RXD0: U9.8 (RXD0/MODE0); also elsewhere on the board
/RMII0_RXD1: U9.7 (RXD1/MODE1); also elsewhere on the board
/RMII0_RXERR: U9.10 (RXER/PHYADO); also elsewhere on the board
/RMII0_TXD0: U9.17 (TXD0); also elsewhere on the board
/RMII0_TXD1: U9.18 (TXD1); also elsewhere on the board
/RMII0_TXEN: U9.16 (TXEN); also elsewhere on the board
/ethernet/PHY_RXN: R32.2, T1.8 (TD2-), U9.22 (RXN)
/ethernet/PHY_RXP: R31.2, T1.6 (TD2+), U9.23 (RXP)
/ethernet/PHY_TXN: R30.2, T1.3 (TD1-), U9.20 (TXN)
/ethernet/PHY_TXP: R29.2, T1.1 (TD1+), U9.21 (TXP)
/ethernet/RXN: J4.6 (RXN), T1.9 (TX2-)
/ethernet/RXP: J4.3 (RXP), T1.11 (TX2+)
/ethernet/TXN: J4.2 (TXN), T1.14 (TX1-)
/ethernet/TXP: J4.1 (TXP), T1.16 (TX1+)
/ethernet/led1_regoff: R23.1, R24.2, U9.3 (LED1/REGOFF)
/ethernet/led2_nintsel: J4.10, R26.1, U9.2 (LED2/~NINTSEL)
/ethernet/xt_in: C53.1, U9.5 (XTAL1/CLKLN), Y3.1
/ethernet/xt_out: C52.1, U9.4 (XTAL2), Y3.2
/rst#: U9.15 (~NRST); also elsewhere on the board
Earth: C54.2, C59.2, R35.2
GND: C50.2, C51.2, C52.2, C53.2, C55.2, C56.2, C57.2, C58.2, C59.1, C62.2, C63.2, C64.2, C65.2, R22.1, R25.2, R26.2, R35.1, U9.25 (VSS); also elsewhere on the board
unnamed: C54.1, R27.2, R28.2, R33.1, R34.1
unnamed: J4.4, J4.5, R34.2
unnamed: J4.7, J4.8, R33.2
unnamed: J4.9, R25.1
unnamed: J4.11, R23.2
unnamed: R27.1, T1.15 (CT1_15)
unnamed: R28.1, T1.10 (CT2_10)
unnamed: R22.2, U9.24 (RBIAS)
VDDA: C55.1, C56.1, C57.1, C58.1, C63.1, C64.1, J4.12, L2.2, R24.1, R29.1, R30.1, R31.1, R32.1, T1.2 (CT1_2), T1.7 (CT2_7), U9.1 (VDD2A), U9.19 (VDD1A)

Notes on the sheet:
Decouping capacitors
25MHz crystal
Ethernet PHY
Digital to analog rail
Ethernet magnetics + RJ45
